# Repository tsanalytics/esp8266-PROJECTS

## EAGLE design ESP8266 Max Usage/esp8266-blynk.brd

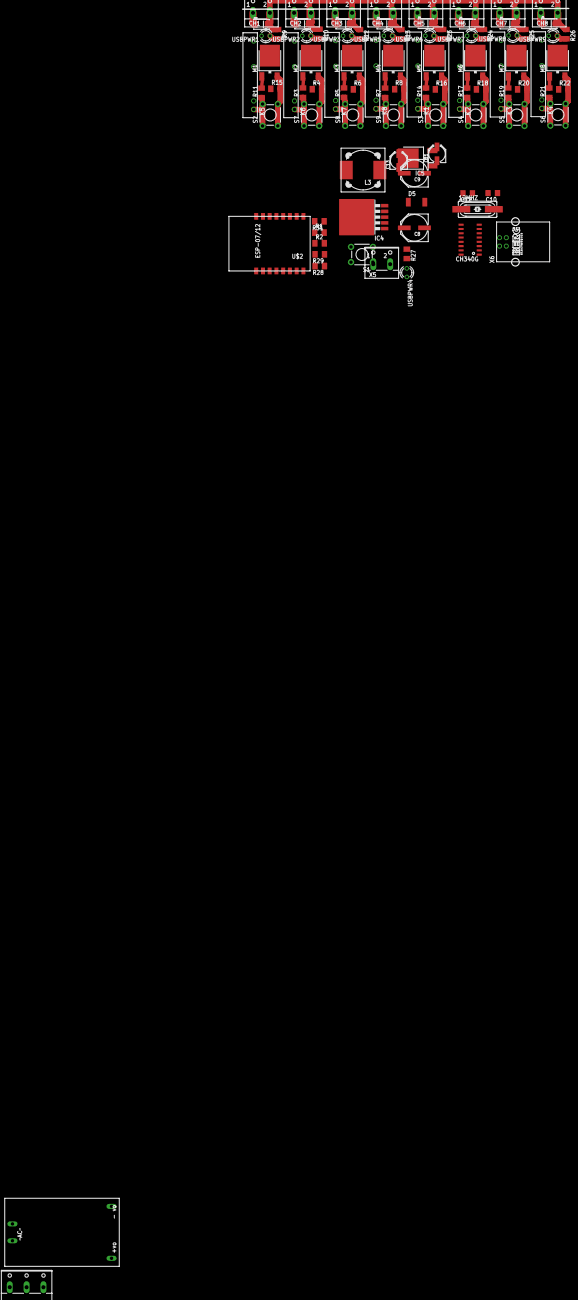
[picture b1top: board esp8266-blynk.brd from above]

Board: 2 copper layers, 97 parts (0 on the bottom side), 51 nets.

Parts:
12MHZ: HC49UP
AC-INPUT: W237-103
C8, C9: PANASONIC_E
C10, C12: 0.1U; C1206
C11, C13: PANASONIC_C
CH1, CH2, CH3, CH4, CH5, CH6, CH7, CH8: W237-102
D1, D2, D3, D4, D6, D7, D8, D10: SMA-DIODE_ALT
D5: SOD87
IC4: TO263-5
IC5: LD117ADT33TR; DPACK
K1, K2, K3, K4, K5, K6, K7, K8: AQG12105; AQG
L3: DR127
M1, M2, M3, M4, M5, M6, M7, M8: IRLR024N; TO252
R1, R2, R9, R10, R12, R13, R23, R24, R25, R26, R27, R28, R29, R31: 1K; M1206
R3, R5, R7, R11, R14, R17, R19, R21: 10R; M1206
R4, R6, R8, R15, R16, R18, R20, R22: 10K; M1206
S1, S2, S3, S4, S5, S6, S7, S8, S9: TACTILE-PTH
U$1: HLK-PM01
U$2: ESP8266_ESP-12; ESP8266-ESP12
U$4: CH340G; SOIC16
USBPWR1, USBPWR2, USBPWR3, USBPWR4, USBPWR5, USBPWR6, USBPWR7, USBPWR8, USBPWR9: LED3MM
X5: W237-102
X6: PN61729

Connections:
0: R2.1, U$2.4
2: R1.1, U$2.3
3.3V: C13.+, IC5.4, R1.2, R2.2, R28.1, R29.1, U$2.16, U$4.4, U$4.16
5V: C9.+, C11.+, IC4.4, IC5.3, L3.2, R27.1, U$1.+VO, X6.1
15: R31.1, U$2.2
AC-L: AC-INPUT.1, K1.O1, K2.O1, K3.O1, K4.O1, K5.O1, K6.O1, K7.O1, K8.O1, U$1.AC2
AC-N: AC-INPUT.2, U$1.AC1
CH1: K5.-, R11.1, S2.1, S2.2
CH2: K6.-, R3.1, S7.1, S7.2
CH3: K7.-, R5.1, S8.1, S8.2
CH4: K8.-, R7.1, S9.1, S9.2
CH5: K1.-, R14.1, S3.1, S3.2
CH6: K2.-, R17.1, S4.1, S4.2
CH7: K3.-, R19.1, S5.1, S5.2
CH8: K4.-, R21.1, S6.1, S6.2
CHRX: U$2.8, U$4.3
CHTX: U$2.7, U$4.2
D+: U$4.5, X6.3
D-: U$4.6, X6.2
GND: C8.-, C9.-, C10.1, C11.-, C12.1, C13.-, D5.2, IC4.3, IC4.5, IC4.6, IC5.1, M1.2, M2.2, M3.2, M4.2, M5.2, M6.2, M7.2, M8.2, R4.2, R6.2, R8.2, R15.2, R16.2, R18.2, R20.2, R22.2, R31.2, S1.3, S1.4, S2.3, S2.4, S3.3, S3.4, S4.3, S4.4, S5.3, S5.4, S6.3, S6.4, S7.3, S7.4, S8.3, S8.4, S9.3, S9.4, U$1.-VO, U$2.1, U$4.1, USBPWR4.K, X5.1, X6.4
unnamed: M2.1, R3.2, R4.1
unnamed: M3.1, R5.2, R6.1
unnamed: M4.1, R7.2, R8.1
unnamed: R9.2, USBPWR1.A
unnamed: R10.2, USBPWR2.A
unnamed: R12.2, USBPWR3.A
unnamed: R13.2, USBPWR5.A
unnamed: D5.1, IC4.2, L3.1
unnamed: R27.2, USBPWR4.A
unnamed: 12MHZ.1, C12.2, U$4.7
unnamed: 12MHZ.2, C10.2, U$4.8
unnamed: M5.1, R14.2, R16.1
unnamed: R28.2, U$2.11
unnamed: M6.1, R17.2, R18.1
unnamed: M7.1, R19.2, R20.1
unnamed: M8.1, R21.2, R22.1
unnamed: R23.2, USBPWR6.A
unnamed: R24.2, USBPWR7.A
unnamed: R25.2, USBPWR8.A
unnamed: R26.2, USBPWR9.A
unnamed: M1.1, R11.2, R15.1
OUT1: CH1.1, D10.A, K5.O2, M1.3, USBPWR1.K
OUT2: CH2.1, D1.A, K6.O2, M2.3, USBPWR2.K
OUT3: CH3.1, D2.A, K7.O2, M3.3, USBPWR3.K
OUT4: CH4.1, D3.A, K8.O2, M4.3, USBPWR5.K
OUT5: CH5.1, D4.A, K1.O2, M5.3, USBPWR6.K
OUT6: CH6.1, D6.A, K2.O2, M6.3, USBPWR7.K
OUT7: CH7.1, D7.A, K3.O2, M7.3, USBPWR8.K
OUT8: CH8.1, D8.A, K4.O2, M8.3, USBPWR9.K
RESET: R29.2, S1.1, S1.2, U$2.9
VM: C8.+, CH1.2, CH2.2, CH3.2, CH4.2, CH5.2, CH6.2, CH7.2, CH8.2, D1.C, D2.C, D3.C, D4.C, D6.C, D7.C, D8.C, D10.C, IC4.1, R9.1, R10.1, R12.1, R13.1, R23.1, R24.1, R25.1, R26.1, X5.2

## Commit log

2015-04-09 :boom::camel: Added .gitattributes & .gitignore files
2015-04-09 Added ESP-12 with single relay
2015-04-22 brd modifications
2015-06-20 lcdpanel
2015-10-03 Added new tested PCB layout
2016-01-27 Added 8ch version wip

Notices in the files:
parts and their libraries:
SparkFun-DiscreteSemi: Licensing: CC v3.0 Share-Alike You are welcome to use this library for commercial purposes.
